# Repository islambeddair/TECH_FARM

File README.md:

# TECH_FARMMoisture Sensor

General Overview:
Soil moisture sensor measure the volumetric water content in soil. Since the direct gravimetric measurement of free soil moisture requires removing, drying, and weighting of a sample, soil moisture sensors measure the volumetric water content indirectly by using some other property of the soil, such as electrical resistance, dielectric constant, or interaction with neutrons, as a proxy for the moisture content. The relation between the measured property and soil moisture must be calibrated and may vary depending on environmental factors such as soil type, temperature, or electric conductivity. Reflected microwave radiation is affected by the soil moisture and is used for remote sensing in hydrology and agriculture. Portable probe instruments can be used by farmers or gardeners.
Applications:
Agriculture:
Measuring soil moisture is important for agricultural applications to help farmers manage their irrigation systems more efficiently. Knowing the exact soil moisture conditions on their fields, not only are farmers able to generally use less water to grow a crop, they are also able to increase yields and the quality of the crop by improved management of soil moisture during critical plant growth stages.
Landscape irrigation:
In urban and suburban areas, landscapes and residential lawns are using soil moisture sensors to interface with an irrigation controller. Connecting a soil moisture sensor to a simple irrigation clock will convert it into a "smart" irrigation controller that prevents irrigation cycles when the soil is already wet, e.g. following a recent rainfall event.
Golf courses are using soil moisture sensors to increase the efficiency of their irrigation systems to prevent over-watering and leaching of fertilizers and other chemicals into the ground.
Research:
Soil moisture sensors are used in numerous research applications, e.g. in agricultural science and horticulture including irrigation planning, climate research, or environmental science including solute transport studies and as auxiliary sensors for soil respiration measurements.

	We will use moisture sensor in agricultural applications. 
Hardware Overview:
The Soil Moisture Sensor is pretty straightforward when it comes to hookup. You need to supply VCC and GND. We recommend not powering the sensor constantly to prevent oxidation of the probes (more on this in a bit). You will get a SIG out, which will be between almost VCC and GND, depending on the amount of water in the soil. The two probes are acting as a variable resistor – more water in the soil means better conductivity and results in a lower resistance and a higher SIG out. Your analog readings will vary depending on what voltage you use for Vcc as well as the resolution of your ADC pins.

First: design the moisture sensor by using EAGLE program.

•	EAGLE schematic for moisture sensor.

•	EAGLE board for moisture sensor.

Second:  made (PCB) for moisture sensor.
 
•	Moisture sensor

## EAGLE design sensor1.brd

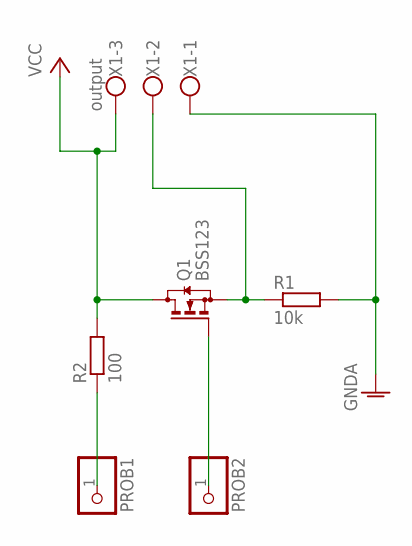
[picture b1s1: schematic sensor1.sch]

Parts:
PROB1, PROB2: PINHD-1X1; 1X01
Q1: BSS123; SOT23
R1: 10k; R1206W
R2: 100; R1206W
X1: output; W237-103

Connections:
GNDA: R1.2, X1.1
unnamed: PROB1.1, R2.1
unnamed: PROB2.1, Q1.1 (G)
unnamed: Q1.2 (S), R1.1, X1.2
VCC: Q1.3 (D), R2.2, X1.3

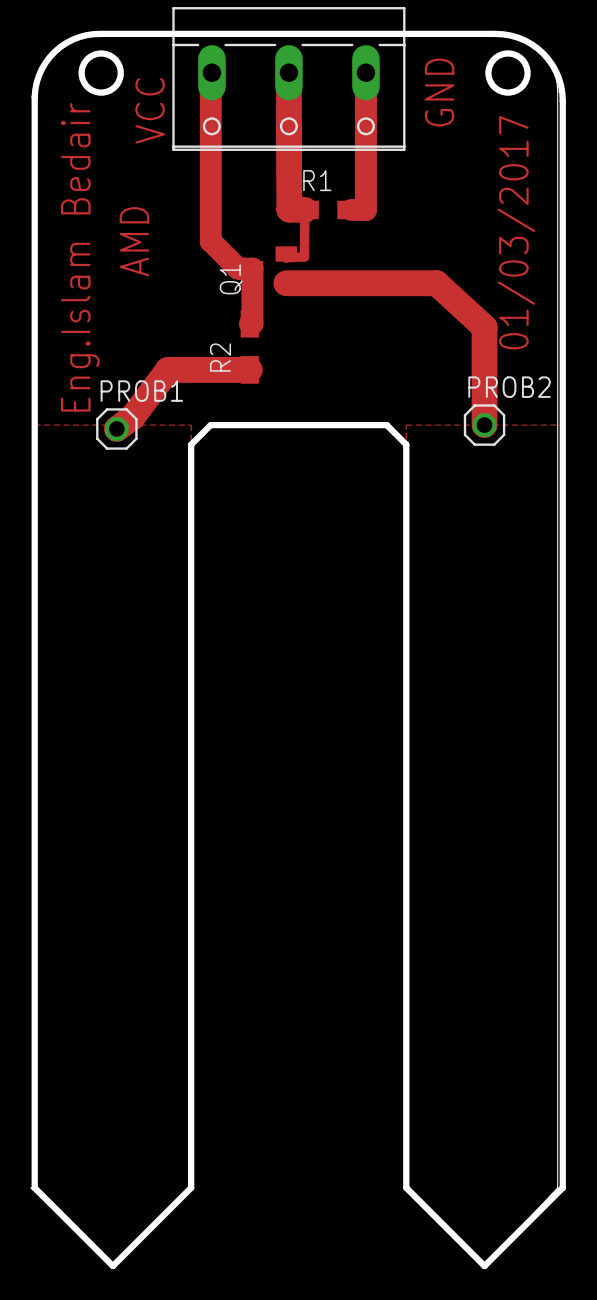
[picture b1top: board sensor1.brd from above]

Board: 2 copper layers, 34.3 x 80.0 mm, 6 parts (0 on the bottom side), 5 nets.
